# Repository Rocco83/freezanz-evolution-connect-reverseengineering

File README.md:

# Freezanz **Zhalt Evolution Connect** — Reverse‑Engineering README

# Attenzione: questo README è stato creato con IA varie e contiene degli errori, sopratutto tutti i voltaggi sono da verificare. Non è sicuro affidarsi a questo progetto, sopratutto per la parte elettrica.

## Avvertenza legale

*Documento redatto esclusivamente a fini di studio, analisi tecnica e interoperabilità (art. 5 DLGS 518/92). L’autore declina ogni responsabilità per usi impropri o violazioni di licenze/marchi.*

---

## Scopo del documento

Raccogliere e mantenere una descrizione completa di **pin‑out**, **connettori** e **I/O** della scheda elettronica **Zhalt Evolution Connect** per lo sviluppo di firmware/software alternativi.

---

## Stato del lavoro

| Versione | Data (EU/Rome) | Autore               | Note brevi                                                                   |
| -------- | -------------- | -------------------- | ---------------------------------------------------------------------------- |
| 0.5      | 2025‑05‑13     | ChatGPT + Rocco83    | Sostituita tabella pin‑out ESP32 con layout basato su LastMinuteEngineer + mapping Freezanz |
| 0.6      | 2026‑03‑12     | Rocco83 + Claude     | Mappatura completa J3 (I2C expansion), J8 (LED ext), P2 (sensor input), correzione P1 |
| 0.7      | 2026‑09‑15     | Rocco83 + Claude     | R452/R455 identificati come pull-up 3K3 (era "290 Ω serie"); corretta tabella pin‑out ESP32; P1 pin 1 = P+ confermato; rimossi blocchi duplicati; chiarito che la 230 VAC non è su questa scheda |

---

## Materiale di riferimento

* Foto PCB fronte/retro (repository)
* **Datasheet ESP32‑WROOM‑32E** (Espressif)
* Articolo di riferimento pin‑out: ["ESP32‑WROOM‑32 Pinout Reference"](https://lastminuteengineers.com/esp32-wroom-32-pinout-reference/) — LastMinuteEngineers 🎓 — immagine riprodotta nella sezione pin‑out
* Manuale d’uso Freezanz (in attesa)
* Foto prodotto: 

---

## Riepilogo connettori esterni
| Rif.            | Tipo / passo           | Pin ↓                        | Segnale         | Tensione       | Descrizione |
|-----------------|------------------------|------------------------------|-----------------|----------------|-------|
| **J1 (DC_IN)**  | Jack barrel Ø2.1 mm    | Tip = **V+**, Sleeve = GND | 12 V DC         | Ingresso alimentazione continua; negativo a massa, positivo protetto da **D1** e instradato al bus **P+** e **B+**, oltre a P1 via **H6** |
| **PUMP**        | Fast-on 2 p            | **PUMP P (P+) / PUMP N (P-)**   | 12 VCC | Rele` pompa nebulizzatore usa la stessa VCC del jack J1, GND mediato da IO27 (da confermare) |
| **BATT**        | Fast-on 2 p            | **BATT P (B+)  / BATT N (B-)**  | 12 VCC | Backup battery (condensatore 16V 68000 uF); **B+** è solidale alla rail **P+** |
| **P1**          | JST-XH 3 p             | 1 = **P+ (12V via H6)**, 2 = GND, 3 = sensor input → R71 (38KΩ) → R107 (0Ω) → GPIO5 | 12V / 0-3.3V | Sensore dry contact: aperto = HIGH su GPIO5, chiuso a GND = LOW. 38KΩ protegge GPIO5 da tensioni >3.3V |
| **J3**          | Pin header 2×4 (NP)    | vedi sezione dedicata        | 3.3V / I2C      | Porta espansione I2C + GPIO. Non collegata di serie. |
| **J8 (LED_EXT)**| Pin header 5 p (NP)    | vedi sezione dedicata        | 12V             | Connettore LED esterni. Non collegato di serie. |
| **P2**          | JST-XH 3 p (NP)        | 1 = 12V, 2 = GND, 3 = sensor input → R67 (38KΩ) → R106 (0Ω) → GPIO15 | 12V / 0-3.3V | Secondo ingresso sensore dry contact, stesso schema di P1. Non collegato di serie. |

### Silkscreen power rail labels (bottom edge)
| Label serigrafia | Rail / Signal                                                                       |
|------------------|-------------------------------------------------------------------------------------|
| **P+**           | “PUMP P” – Positive supply rail (shared with **B+** and **J1 V+**)                   |
| **P-**           | “PUMP N” – Return/ground for pump                                                   |
| **B+**           | “BATT P” – Battery positive (internally tied to **P+**)                             |
| **B-**           | “BATT N” – Battery negative                                                         |

## Connettore **J3** — Header espansione I2C + GPIO

J3 è un pin header 2×4 (8 pin totali) non popolato di serie. Espone il bus I2C
dell'ESP32 con pull-up dedicati, alimentazione e due GPIO aggiuntivi.
Progettato per collegare moduli I2C esterni (display, sensori) o periferiche digitali.

| Pin J3 | Segnale         | Percorso                                      | Note |
|--------|-----------------|-----------------------------------------------|------|
| 1      | VCC / BATT+     | Diretta dalla rail P+                         | Alimentazione 12V |
| 2      | VCC filtrato    | Via resistenza 0.2Ω (jumper/sense)            | VCC con lieve filtraggio |
| 3      | VCC 3.3v        | Diretta da pin 3.3v ESP32                     | VCC per i2c esterno |
| 4      | GND             | —                                             | Riferimento comune |
| 5      | SDA (GPIO21)    | Via R65 (120Ω)                                | I2C Data |
| 6      | GPIO5           | Via R36 (470Ω)                                | Condiviso con P1 pin 3 (sensore acqua) |
| 7      | SCL (GPIO22)    | Via R66 (120Ω)                                | I2C Clock |
| 8      | GPIO15          | Via R89 (470Ω) → R106 (0Ω)                   | GPIO generico. Boot-strapping: deve essere HIGH al reset |

### Note I2C su J3

- I pull-up su SCL/SDA sono già presenti e **sempre attivi**: **R452 = 3K3 su SCL**,
  **R455 = 3K3 su SDA**, entrambe verso la rail 3.3 V dell'ESP32 — la stessa rail
  esposta su pin 3. Il pin 3 è una derivazione di quella rail, **non** un
  interruttore: non serve alimentarlo per abilitare i pull-up. Confermato a
  multimetro (vedi "R452 / R455" più sotto).
- Per usare il bus I2C su J3: collegare VCC a pin 1 o 2, GND a pin 4,
  SDA a pin 5, SCL a pin 7. Il pin 3 **fornisce** 3.3 V al dispositivo esterno:
  è un'uscita derivata dalla rail dell'ESP32, non un ingresso da alimentare.
- GPIO5 (pin 6) è condiviso con il sensore acqua su P1: non usare
  contemporaneamente P1 e J3 pin 6 per segnali distinti.
- GPIO15 (pin 8) è un boot-strapping pin: deve essere HIGH al boot.
  La resistenza R89 da 470Ω protegge il GPIO ma non sostituisce un pull-up
  esterno se il dispositivo collegato potrebbe portare la linea a GND durante il boot.

---

## Connettore **J8** — LED esterni

J8 è un pin header da 5 pin non popolato di serie. Espone i segnali dei tre
LED di stato della board (D7 bicolore e D3) verso l'esterno, permettendo
di collegare LED remoti su pannello frontale o indicatori visivi in posizione
accessibile. Le resistenze di limitazione corrente sono già presenti sulla board.

| Pin J8 | Segnale           | Percorso            | Note |
|--------|-------------------|---------------------|------|
| 1      | 12V (anodo comune)| Rail P+             | Alimentazione LED |
| 2      | Catodo D7 Rosso   | Via ~500Ω           | LED rosso = allarme |
| 3      | Catodo D7 Verde   | Via ~500Ω           | LED verde = pronto |
| 4      | Catodo D3         | Via ~400Ω           | LED stato (blu sulla board) |
| 5      | GND               | —                   | Riferimento |

### Note J8

- Le resistenze di dropping sono già sulla board: collegare LED esterni
  direttamente senza aggiungere resistenze aggiuntive.
- Corrente LED stimata con 12V: (12 - Vf) / R ≈ 20-25mA per LED standard.
- I LED interni D7 e D3 rimangono attivi in parallelo con quelli esterni.

---

## Connettore **P2** — Secondo ingresso sensore

P2 è un connettore JST-XH 3 pin non collegato di serie. Ha lo stesso schema
elettrico di P1: permette di collegare un sensore dry contact a 12V il cui
stato viene letto da GPIO15 dell'ESP32.

| Pin P2 | Segnale    | Percorso                              | Note |
|--------|------------|---------------------------------------|------|
| 1      | 12V        | Rail P+                               | Alimentazione/riferimento sensore |
| 2      | GND        | —                                     | Riferimento comune |
| 3      | Sensor in  | → R67 (38KΩ) → R106 (0Ω) → GPIO15    | Input dry contact |

### Schema di funzionamento P2

Identico a P1: il sensore è un contatto pulito (dry contact) che va a GND
quando attivo. La resistenza R67 da 38KΩ protegge GPIO15 da tensioni superiori
a 3.3V. R103 è un footprint alternativo non popolato.

- **Contatto aperto** (sensore non attivo): GPIO15 = HIGH
- **Contatto chiuso a GND** (sensore attivo): GPIO15 = LOW

GPIO15 è un boot-strapping pin (deve essere HIGH al boot): verificare che
il sensore collegato non porti la linea a GND durante l'accensione.

---

## IC29 — identification

**Package**: MCP7940M Low-Cost I2 C™ Real-Time Clock/Calendar with SRAM
The routing of **GPIO21 / GPIO22** (I²C) go to the **IC29 is an I²C real‑time clock (RTC)**

### Associated timing element

| Ref‑des | Mark code  | Type                           | Connection                                                        |
| ------- | ---------- | ------------------------------ | ----------------------------------------------------------------- |
| **Y2**  | “32 C 040” | 32.768 kHz tuning‑fork crystal | Pins X1/X2 of IC29 (through short tracks) — provides RTC timebase |

This has been confirmed
```
[23:30:15.223][C][i2c.idf:093]: I2C Bus:
[23:30:15.230][C][i2c.idf:094]:   SDA Pin: GPIO21
[23:30:15.230][C][i2c.idf:094]:   SCL Pin: GPIO22
[23:30:15.230][C][i2c.idf:094]:   Frequency: 100000 Hz
[23:30:15.230][C][i2c.idf:104]:   Recovery: bus successfully recovered
[23:30:15.232][C][i2c.idf:114]: Results from bus scan:
[23:30:15.233][C][i2c.idf:120]: Found device at address 0x6F
```

---

## Alimentazione — la 230 VAC non è su questa scheda

Su questa scheda **non è presente la rete 230 VAC.** Il trasformatore è su una
**scheda esterna separata**, che fornisce 12 V continui all'ingresso `J1 (DC_IN)`.
Di conseguenza tutto ciò che sta a bordo — pompa inclusa — lavora a 12 V.

| Elemento | Dove | Note |
| -------- | ---- | ---- |
| Alimentatore 230 VAC → 12 V | **scheda esterna** | fuori dallo scopo di questo documento |
| `J1 (DC_IN)` | questa scheda | jack barrel Ø2.1 mm, ingresso 12 V |
| Rail `P+` | questa scheda | 12 V distribuiti a pompa, buzzer, LED, P1/P2, J3 pin 1 |
| `BATT` (`B+` / `B-`) | questa scheda | condensatore di backup 16 V 68000 µF, solidale a `P+` |

La pompa nebulizzatore è quindi pilotata **a 12 V** tramite relè, non a 230 VAC.

**Tutto ciò che arriva dall'esterno è a 12 V** (confermato). I 3.3 V per l'ESP32
sono generati a bordo da uno stadio step-down dai 12 V della rail `P+`; è la
stessa rail 3.3 V esposta su `J3` pin 3 e su cui sono legati i pull-up I²C
R452/R455. Quindi su questa scheda esistono due sole tensioni: **12 V** in
ingresso e distribuzione, **3.3 V** per la logica.

---

## Connettore **J4** — Header di programmazione ESP32

| Pin J1 | Segnale scheda   | Collegare FTDI        | Pad modulo | Descrizione                         |
| ------ | ---------------- | --------------------- | ---------- | ----------------------------------- |
| 1      | **BOOT / GPIO0** | — (strap)             | Pin 25     | LOW all’accensione → bootloader     |
| 2      | **TX0 / GPIO1**  | RX FTDI               | Pin 35     | UART console 115 200 8N1            |
| 3      | **RX0 / GPIO3**  | TX FTDI               | Pin 34     | UART console                        |
| 4      | **VCC 3,3V**    | 3 V 3 FTDI (≥ 500 mA) | —          | Alimenta la logica durante il flash |
| 5      | **EN / RESET**   | —                     | Pin 3      | CHIP\_EN — LOW ⇒ reset              |
| 6      | **GND**          | GND FTDI              | —          | Riferimento comune                  |

> **Procedura di flash**
>  1 Disconnettere la scheda da potenza.
>  2 Collegare FTDI 3 V 3.
>  3 Tenere BOOT e EN LOW, quindi rilasciare EN → HIGH, poi BOOT → HIGH.
>  4 `esptool.py --chip esp32 --baud 921600 write_flash 0x0 firmware.bin`

---

## Pin‑out **ESP32‑WROOM‑32E** (basato su LastMinuteEngineer + mapping Freezanz)

*Immagine: [ESP32‑WROOM‑32 Pinout Reference](https://lastminuteengineers.com/esp32-wroom-32-pinout-reference/) — © LastMinuteEngineers, riprodotta come riferimento tecnico. La tabella seguente mappa questi pin sulle funzioni Freezanz.*

| Pin # | Pin Label | GPIO |**Freezanz Function** |Tipo |Note |Reason |Safe to use? |
| - | ---------- | ---- |------------------------- |--------------- |------ |----------- |------------ |
| 1 | GND | — | — | — | Ground pad | Ground | ✔︎ |
| 2 | 3V3 | — | — | — | Main 3.3 V rail | Power supply | ✔︎ |
| 3 | **EN** | — | **Reset (CHIP_EN)** | Input | J1‑5 · LOW ⇒ reset | Chip enable / strapping | ⚠︎ |
| 4 | SENSOR\_VP | 36 | — | ADC input |  TBD — SW probe   | Input‑only | ✗ |
| 5 | SENSOR\_VN | 39 | — | ADC input |  TBD — SW probe   | Input‑only | ✗ |
| 6 | IO34 | 34 | N/C | ADC / input | Footprint **D5** (non popolato) | Input‑only | ✗ |
| 7 | IO35 | 35 | N/C | ADC / input | Footprint **D45** (non popolato) | Input‑only | ✗ |
| 8 | IO32 | 32 | **SW3** (Start/Stop) | Input (PULL‑UP) | Pulsante LOW ⇒ pressed   | — | ✔︎ |
| 9 | IO33 | 33 | **SW2** (On/Off) | Input (PULL‑UP) | Pulsante LOW ⇒ pressed | — | ✔︎ |
| 10 | IO25 | 25 | **LED D7** (Red) | Output | High = ON | — | ✔︎ |
| 11 | IO26 | 26 | **Buzzer** | PWM Out | PWM Out (frequenze udibili testate: 1.5 / 2.5 / 3 / 4 / 5 kHz) | — | ✔︎ |
| 12 | IO27 | 27 | — | — | R24->R23->Q7->X20->P- | — | ✔︎ |
| 13 | IO14 | 14 | — | — | Non usato (VERIFICARE) | — | ✔︎ |
| 14 | IO12 | 12 | N/C | — | Collegato a **R35** (N/C) | Strapping · LOW al boot | ⚠︎ |
| 15 | GND | — | — | — | Non usato sulla scheda (pad GND) | Ground | ✔︎ |
| 16 | IO13 | 13 | **IPOTESI** SW2_DRV (via Q4, accensione via software) - routing R27 -> R9 -> Q4 (piedino destro) -> Q4 (piedino centrale) -> R100 -> R71(?) -> Piedino vicino D11 SW2 ON/OFF | — | — | Strapping | ⚠︎ | Non disponibile |
| 17 | SD2 | 9 | — | — | Non disponibile | SPI flash interno | ✗ |
| 18 | SWP/SD3 | 10 | — | — | Non disponibile | SPI flash interno | ✗ |
| 19 | SCS/CMD | 11 | — | — | Non disponibile | SPI flash interno | ✗ |
| 20 | SCK/CLK | 6 | — | — | Non disponibile | SPI flash interno | ✗ |
| 21 | SDO/SD0 | 7 | — | — | Non disponibile | SPI flash interno | ✗ |
| 22 | SDI/SD1 | 8 | — | — | Non disponibile | SPI flash interno | ✗ |
| 23 | IO15 | 15 | **Expansion line (J3‑8)** | I/O | Via **R91** (not fitted) & **C30→GND**, then through **R89 470 Ω** to connector **J3‑pin 8** (header currently unpopulated) – reserved for future external signal | Boot‑strapping pin (must be **HIGH** at reset) | ⚠︎ |
| 24 | IO2 | 2 | **Line via R95 → D9** | I/O | Series **R95 150 Ω** to node with **D9** and pulldown **R76 8.3 kΩ**; D9 centre via **R8 10 kΩ** to GND. Purpose TBD (possible indicator or external sense). | Must be LOW at boot (strapping) | ⚠︎ |
| 25 | IO0 | 0 | **BOOT (J1‑1)** | Input | LOW al reset ⇒ flash | Boot / flash mode | ⚠︎ |
| 26 | IO4 | 4 | — | — | Non usato | — | ✔︎ |
| 27 | IO16 | 16 | — | — | Non usato | — | ✔︎ |
| 28 | IO17 | 17 | — | — | Non usato | — | ✔︎ |
| 29 | IO5 | 5 | **P1‑1** | TBD input | Connettore P1 pin sinistro | Must be HIGH at boot | ⚠︎ |
| 30 | IO18 | 18 | **LED D6** (Green) | Output | High = ON | — | ✔︎ |
| 31 | IO19 | 19 | **LED D3** (Blue) | Output | High = ON | — | ✔︎ |
| 33 | IO21 | 21 | **RTC I²C SDA (addr 0x6F; clock ticking)** | I/O | **SDA** which keeps the clock through IC29 & Y2. Pull-up: **R455 = 3K3 → 3V3** (misurato). Verso l'RTC: **R70 220 Ω** → IC29. Verso J3-5: **R65 120 Ω** | Default I²C **SDA** | ✔︎ |
| 34 | RXD0 | 3 | **UART RX0 (J1‑3)** | Input | 115 200 8N1 console | UART / flashing | ⚠︎ |
| 35 | TXD0 | 1 | **UART TX0 (J1‑2)** | Output | 115 200 8N1 console | UART / flashing | ⚠︎ |
| 36 | IO22 | 22 | **RTC I²C SCL (addr 0x6F; clock ticking)** | I/O | **SCL** which keeps the clock through IC29 & Y2. Pull-up: **R452 = 3K3 → 3V3** (misurato). Verso l'RTC: **R69 220 Ω** → IC29. Verso J3-7: **R66 120 Ω** | Default I²C **SCL** | ✔︎ |
| 37 | IO23 | 23 | **LED D7** (Green) | Output | High = ON | — | ✔︎ |
| 38 | GND | — | — | — | Non usato sulla scheda (pad GND termico) | Ground | ✔︎ |

---

## Indicatori & pulsanti

### LED

| LED                | GPIO                    | Stato                           | Significato             |
| ------------------ | ----------------------- | ------------------------------- | ----------------------- |
| **D6** (Verde)     | 18                      | Solid                           | Nebulizzazione in corso |
|                    |                         | Blink                           | Pulse cycle             |
| **D3** (Blu)       | 19                      | Solid                           | Wi‑Fi attivo            |
|                    |                         | Blink                           | Wi‑Fi connesso          |
| **D7** (Bi‑colore) | 25 (Rosso) / 23 (Verde) | Rosso = allarme, Verde = pronto |                         |

### Pulsanti

| Pulsante | GPIO | Funzione   | Note            |
| -------- | ---- | ---------- | --------------- |
| **SW2**  | 33   | ON/OFF     | Pull‑up interno |
| **SW3**  | 32   | START/STOP | Pull‑up interno |

### Buzzer

| GPIO | Funzione     | Segnale           |
| ---- | ------------ | ----------------- |
| 26   | Piezo buzzer | PWM 2‑4 kHz (TBD) |

## Buzzer circuit — detail

### Components

| Ref | Value | Function |
|-----|-------|----------|
| Q6 | BST82 (marking "68W 02") | N-Channel Enhancement Mode Vertical DMOS FET, SOT-23 |
| R14 | 4K7 | Series resistor on GPIO side — limits gate current |
| R13 | 2K2 | Pull-down resistor to GND — voltage divider, stabilizes gate |

### Wiring

- **Piezo (+)**: connected directly to **P+ rail (12V)** with no components in between
- **Piezo (-)**: connected to **Q6 Drain**
- **Q6 Source**: GND
- **Q6 Gate**: GPIO26 → R14 (4K7) → R13 (2K2) → GND

### Gate voltage

With GPIO26 HIGH (3.3V), the R14/R13 divider brings the gate to:

```
Vgate = 3.3V × (2200 / (4700 + 2200)) ≈ 1.05V
```

Sufficient to exceed the BST82 Vgs threshold (~0.8–1.5V typical for DMOS FET).

### Volume modulation — analysis and hypotheses

FFT measurements on audio recordings at 3 distinct volume levels show that
the RMS amplitude varies by approximately **10×** between minimum and maximum volume,
confirming that the original firmware does effectively modulate volume.

| Level | Measured RMS | Dominant frequency |
|-------|--------------|--------------------|
| vol1 (low)    | ~0.004 | 5200 Hz (2× harmonic of 2600 Hz) |
| vol2 (medium) | ~0.025 | 5200 Hz (2× harmonic of 2600 Hz) |
| vol3 (high)   | ~0.055 | 5200 Hz (2× harmonic of 2600 Hz) |

Since the +12V is directly connected to the piezo with no control components,
modulation can only occur **on the Q6 gate**.

Technical hypotheses for volume modulation, in order of likelihood:

1. **Hardware DAC (GPIO26 = DAC2)** — the original firmware uses the DAC instead
   of PWM to generate a variable DC voltage on the gate, driving the BST82 into
   its linear region and modulating the Drain-Source resistance. To verify:
   measure Q6 gate with oscilloscope at different volume levels with original
   firmware — if the DC level changes, this hypothesis is confirmed.

2. **Variable PWM duty cycle** — the firmware varies the PWM duty cycle,
   modifying the average conduction time of the BST82. Less likely because
   with a fast-switching MOSFET the effect on perceived volume is limited.

3. **Frequency near/far from piezo resonance** — the piezo responds non-linearly
   to frequency; it sounds louder near its mechanical resonance frequency.
   Partially supported by the variation in dominant frequency measured across levels.

### TODO — oscilloscope verification

- [ ] Measure waveform on Q6 gate with original firmware at min and max volume
- [ ] Check whether DC level on gate changes with volume (confirms DAC hypothesis)
- [ ] Check whether PWM duty cycle changes with volume (confirms variable PWM hypothesis)
- [ ] Measure mechanical resonance frequency of the piezo (volume peak)

## P1 connector — liquid flow sensor

### Description

P1 is a **liquid flow sensor** connected via JST-XH 3-pin connector.
The sensor outputs a signal proportional to liquid flow on the return pin.

### Wiring

| P1 Pin | Signal | Description |
|--------|--------|-------------|
| 1 (pad quadrato) | **P+ (12V via H6)** | Sensor power supply |
| 2 | GND | Ground reference |
| 3 | Sensor input → R71 (38KΩ) → R107 (0Ω) → GPIO5 | Signal return pin |

### Signal behavior

- **Normal state (water flowing)**: return pin at ~9V (HIGH after voltage divider)
- **Fault state (no water)**: return pin pulled to GND (LOW)
- During normal pump activation, multiple state transitions are expected on this pin.

### Voltage protection

The sensor return pin operates at ~9V. Direct connection to GPIO5 (max 3.3V)
would destroy the ESP32. A voltage divider or level shifter **must be present**
between P1 pin 3 and GPIO5 on the PCB — verify resistor values on PCB traces
between P1 connector and GPIO5.

### Pull-down

Since the signal is externally driven (HIGH = ~3.3V after divider, LOW = GND),
the ESP32 internal pull-up must be disabled. An external pull-down resistor
is recommended to guarantee a defined LOW state when the sensor is disconnected.
If a resistor to GND is already present on the PCB on this line, it may be sufficient.

### TODO

- [ ] Identify and measure voltage divider components between P1 pin 3 and GPIO5
- [ ] Determine exact timing pattern of state transitions during normal pump activation
- [ ] Define threshold (duration of LOW) to classify as water fault vs normal transition

---

## Ponticelli / Jumper

| Jumper | Default           | Collega                  | Funzione                                                            |
|--------|-------------------|--------------------------|---------------------------------------------------------------------|
| **H6** | CHIUSO (fabbrica) | **P1-3 (P+)** ↔ **12 VCC**  | Collega il pin 3 del connettore P1 alla linea VCC (DC_IN/BATT P); aprirlo isola P1 dalla VCC esterna |

---

## Tests to perform

### IO13 — Virtual ON/OFF Driver

**Goal**
Verificare che **GPIO13** possa emulare la pressione del pulsante **SW2** (On/Off) tramite il transistor Q4 (BC817-25).

**Test procedure**
1. Inizializza i pin in MicroPython:
   ```python
   from machine import Pin
   import time

   sw2_drv = Pin(13, Pin.OUT)
   sw2_drv.value(0)                       # transistor inizialmente spento

   # GPIO33 normally read the ON/OFF (SW2) button state
   sw2_in = Pin(33, Pin.IN, Pin.PULL_UP)  # legge lo stato del pulsante SW2
   ```

2. Baseline: premi fisicamente SW2 e verifica in REPL:
   ```python
   print("SW2 manual press:", "LOW" if sw2_in.value()==0 else "HIGH")
   ```
   Deve stampare LOW quando premi.

3.	Emulazione: senza toccare il pulsante, esegui:
   ```python
   sw2_drv.value(1)
   time.sleep(0.2)
   sw2_drv.value(0)
   print("SW2 emulated press:", "LOW" if sw2_in.value()==0 else "HIGH")
   ```
   * Controlla che sw2_in.value() ritorni 0 (LOW) durante il pulse.
   * Verifica che l’unità si accenda/spegna come con una pressione fisica.

   3. (Opzionale) Collega un oscilloscopio alla linea SW2 per osservare il fronte netto grazie al feedback R9.

---

IO2 — RTC Square-Wave / Alarm Output

Goal
Confermare che GPIO2 riceva un segnale a 1 Hz dall’MFP/SQW pin dell’RTC MCP7940M attraverso la rete R95 → D9 → R76.

Test procedure
```python
from machine import Pin, I2C
import time

# 1) Inizializza I²C su GPIO21/22
i2c = I2C(0, scl=Pin(22), sda=Pin(21), freq=100000)

# 2) Abilita il square-wave 1 Hz (registro 0x07)
addr = 0x6F
ctrl = i2c.readfrom_mem(addr, 0x07, 1)[0]
ctrl |= 0x10      # SQWE = 1 (enable square-wave)
ctrl &= ~0x03     # RS = 00 (set 1 Hz)
i2c.writeto_mem(addr, 0x6F, bytes([ctrl]))

# 3) Conta i fronti su GPIO2
pulse = Pin(2, Pin.IN)
edges = 0
def on_rise(pin):
    global edges
    edges += 1

pulse.irq(trigger=Pin.IRQ_RISING, handler=on_rise)
time.sleep(5)
print("Edges in 5 s:", edges)  # Atteso ≈ 5
```
* Se conti circa 5 fronti in 5 s, il crystal e l’RTC funzionano.

---

Quando entrambi i test passano, l’emulazione del pulsante e il segnale RTC sono confermati.

---

### R452 / R455 — identificazione pull-up I²C — **RISOLTO (2026-09-15)**

**Esito**: R452 e R455 **sono i pull-up I²C da 3K3**, sempre attivi, verso la
rail 3.3 V dell'ESP32.

| Sigla | Ruolo confermato |
| ----- | ---------------- |
| **R452** | pull-up 3K3 su **SCL** (IO22, pin 36) → 3V3 |
| **R455** | pull-up 3K3 su **SDA** (IO21, pin 33) → 3V3 |

Il valore "290 Ω in serie verso IC29" che compariva nella tabella pin-out ESP32
era **errato** ed è stato corretto. Le resistenze di serie verso J3 sono altre:
**R65 120 Ω** su SDA e **R66 120 Ω** su SCL; verso l'RTC la serie è **R69 220 Ω**.

**Come è stato determinato**

1. Continuità: `SDA breakout → R65 (120 Ω) → pin 33 ESP32`, e
   `SCL breakout → R66 (120 Ω) → pin 36 ESP32`.
2. Continuità: `pin 36 (SCL) → R452 → 3V3` e `pin 33 (SDA) → R455 → 3V3`.
3. Misure a multimetro, coerenti fra loro:
   * pin ESP32 → GND: **3.5 kΩ** (pull-up letto attraverso la rail 3V3 non alimentata)
   * dal lato breakout → 3V3: **3.4 kΩ** su entrambe le linee
     = 3K3 del pull-up + 120 Ω della serie. Conferma incrociata.

**Conseguenze**

* La breakout `freezanz-level-io` **non deve popolare R1/R2** (4k7): i pull-up
  esistono già e sono raggiungibili attraverso J3. Aggiungerne altri
  abbasserebbe troppo la resistenza equivalente.
* I pull-up **non** dipendono dall'alimentazione del pin 3: sono legati in modo
  permanente alla rail 3.3 V della scheda.
* 3K3 è un valore del tutto normale: **questo non spiega i timeout I²C**, che
  restano da indagare altrove (capacità del cavo, rumore condotto dalla rail
  della pompa).

## TODO

* [x] Investigate **IO15 / J3‑8** expansion line: mappato completo, GPIO15 via R89 470Ω → R106 0Ω. Condiviso con P2 pin 3.
* [x] Mappatura completa J3: I2C expansion header con pull-up 3K3, GPIO5, GPIO15.
* [x] Mappatura J8: LED esterni 12V, catodi D7 rosso/verde e D3 esposti con resistenze già in serie.
* [x] Mappatura P2: secondo sensore dry contact su GPIO15, stesso schema P1/GPIO5.
* [x] Correzione P1: pin 1 = 12V (P+ via H6), pin 3 = sensore → R71 38KΩ → R107 0Ω → GPIO5.
* [x] Phase‑2 test: board re‑installed in unit.
* [x] **R452 / R455**: risolti — sono i pull-up I²C da 3K3 (R452 su SCL, R455 su SDA) verso la rail 3.3 V, sempre attivi. Il "290 Ω in serie" era errato. La breakout `freezanz-level-io` non deve popolare R1/R2. Non spiega i timeout I²C.
* [ ] **Tensione reale della rail 12 V**: misurarla. D1 sulla breakout è un P6KE15A, stand-off 12.8 V: se la rail sta sopra (es. 13.8 V) il TVS lavora in perdita e si scalda. I condensatori (C1 25 V) reggono comunque.
* [x] **PUMP è a 12 VCC.** La 230 VAC non è su questa scheda: il trasformatore sta su una scheda esterna che fornisce 12 V a `J1`. Le righe che indicavano 230 VAC erano in blocchi duplicati obsoleti, ora rimossi.
* [ ] SENSOR\_VP/VN: log ADC values in real operation.
* [ ] Draw partial schematic in KiCad.
* [ ] Understand how the serial port of the original firmware is working
* [ ] Understand how to lower the volume of the buzzer

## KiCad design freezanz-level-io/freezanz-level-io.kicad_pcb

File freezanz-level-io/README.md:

# Freezanz level I/O board — rev A

Interface board for eight XKC-Y25-NPN capacitive level sensors, with the CJMCU
MCP23017 module on a socket so it stays swappable. Everything is through-hole:
the only thing needed from the fab house is the bare PCB.

- Board cut: **90 × 50 mm** (enclosure is 95 × 55, so there is margin all round)
- 2 layers, 1.6 mm
- 50 parts to fit, 5 optional footprints left unpopulated

## Files

| File | Contents |
|---|---|
| `freezanz-level-io.kicad_pro` | project — one net class, Default: 0.2 mm track, 0.2 mm clearance |
| `freezanz-level-io.kicad_sch` | full schematic, footprints already assigned |
| `freezanz-level-io.kicad_pcb` | board outline only, 90 × 50 on Edge.Cuts |
| `schema-rev-a.svg` | readable schematic, for review without KiCad |

## Getting started

Nothing in this project contains invented geometry. Symbols and footprints are
referenced by their standard KiCad library names and resolve against your own
installation:

1. **Eeschema** → `Tools → Update Symbols from Library`, select all. The cached
   symbol graphics are replaced by the real ones. Pin coordinates in the file
   already match the KiCad 10 library exactly, so no connection is lost.
2. **PCB editor** → `Tools → Update PCB from Schematic` (F8). All 51 footprints
   are imported from your libraries, stacked at the origin, ready to place.
3. Place and route. The board file carries only the outline.

No ground pour is defined. GND is the largest net (35 connections), so routing
it by hand is real work — a pour on B.Cu would absorb most of it, but that is
your call.

## MCP23017 module socket (CJMCU)

Two 2.54 mm rows on the right, one on the left. Measured: 9 pad positions
inclusive from the left row to the outer right row, so **20.32 mm** left-to-outer
and 17.78 mm left-to-inner.

| | inner right column | outer right column |
|---|---|---|
| 1 | VCC | GND |
| 2 | INTB | INTA |
| 3 | **GPB0 → B0** | GPA0 → A0 |
| 4 | **GPB1 → B1** | GPA1 → A1 |
| 5 | **GPB2 → B2** | GPA2 → A2 |
| 6 | **GPB3 → B3** | GPA3 → A3 |
| 7 | **GPB4 → B4** | GPA4 → A4 |
| 8 | **GPB5 → B5** | GPA5 → A5 |
| 9 | **GPB6 → B6** | GPA6 → A6 |
| 10 | **GPB7 → B7** | GPA7 → A7 |

**Port B, the inner column, carries the level sensors**; port A goes to the `J6`
breakout. `J4` is a 2×10 with odd/even numbering, and the **odd pins are the
inner column** — the one nearer `J3`.

This assignment was wrong on rev A. The board had GND and port A on the inner
column, but the real CJMCU module has **VCC and port B inboard**. Plugging in a
correctly-seated module therefore put VCC on the GND net and destroyed the chip.
Rev B swaps the columns to match. Because the sensors are wired to the inner
column, they now land on port B — which is why the nets are `B0..B7` and the
firmware addresses them as ESPHome `number: 8..15`.

Left row `J3`: `AD2 AD1 AD0 RESET SO CS SDA SCL GND VCC`. Pins 5 and 6 are SPI-only
and stay unconnected.

**The three address pins are called `AD2 AD1 AD0` in this document.** The module
silkscreen prints them as A0/A1/A2 — the *same* names it prints on the port A
pins of the right row, so `A0` appears twice on the module and means two
unrelated things. To avoid that trap: the I²C hardware address inputs are
`AD0..AD2` here, the port A GPIO nets are `A0..A7`. All three `AD` pins are tied
straight to GND, setting the address to **0x20**.

## Input — one IDC connector

A single 2×4 IDC header, extended 1:1 by ribbon cable from the `J3` expansion
header on the Freezanz board. Pinout per the reverse-engineering README rev 0.6;
IDC zig-zag numbering, odd pins on one row, even on the other.

| Pin | Net | Path on the Freezanz board |
|---|---|---|
| 1 | `+12V_RAW` | straight off rail P+ |
| 2 | `+12V_FILT` | through a 0.2 Ω sense/jumper resistor |
| 3 | `+3V3` | straight off the ESP32 3.3 V pin |
| 4 | `GND` | — |
| 5 | `SDA` | GPIO21 through R65, 120 Ω |
| 6 | `GPIO5` | through R36, 470 Ω — shared with the P1 sensor input |
| 7 | `SCL` | GPIO22 through R66, 120 Ω |
| 8 | `GPIO15` | through R89, 470 Ω — boot-strapping pin |

SDA and SCL already carry 120 Ω in series (R65/R66) and 3.3 kΩ pull-ups
(R455 on SDA, R452 on SCL) on the Freezanz side, which is why R1/R2 here stay
unpopulated. Those pull-ups are tied permanently to the ESP32's 3.3 V rail — pin 3
is a tap off that same rail, not a switch, so they are active whenever the
mainboard is powered. Measured from this board: 3.4 kΩ to 3V3 on both lines,
i.e. the 3K3 pull-up plus the 120 Ω series.

GPIO5 and GPIO15 are ESP32 strapping pins that must sit HIGH at reset, so
anything connected to `J8`/`J9` must not hold them low during boot.

`JP2` selects which 12 V feeds the board, centre pin as the output. The 0.2 Ω is
almost certainly a sense shunt rather than a filter, so do not parallel the two
rails; the jumper keeps both options open until that is confirmed.

## Sensor channel (×8)

XKC-Y25-NPN, 4-pin flat connector:

| Pin | Wire | Net |
|---|---|---|
| 1 | black | `SENS_M` — mode select |
| 2 | blue | GND |
| 3 | yellow | signal out |
| 4 | brown | +12V |

```
          +3V3
            |
          [10k]  R21..R28
            |
XH 4p       |          MCP23017
 1 M -------|--------- SENS_M --- JP1 --- GND
 2 GND      |
 3 SIG -[470R]----------.-------- GPB0..GPB7  (nets B0..B7)
        R11..R18
 4 +12V
```

- **470R in series** is the protection that was missing. If the yellow wire ever
  sees 12 V, current into the MCP pin stays under 20 mA instead of destroying it.
  With the sensor's NPN conducting the pin sits around 0.35 V, comfortably inside
  the MCP23017 V_IL of 0.66 V.
- **10k to 3V3** is the pull-up, on the MCP side of the series resistor. The
  sensor output is open-collector, so without it the line floats when dry.
- **`SENS_M`** ties all eight mode pins together. `JP1` open (default) leaves the
  sensors in normal output mode; fitting the jumper pulls all eight to GND and
  inverts every output at once, with no rewiring.

## Power

```
J1.1 +12V_RAW  --+
                 |-- JP2 --> F1 --> +12V --+-- D1 P6KE15A --> GND
J1.2 +12V_FILT --+                         +-- C1 10uF (+ C2 pad, not fitted)
                                           +-- 8x sensor connectors
                                           +-- J8, J9
```

**F1 is a 200 mA fast 5×20 cartridge.** Worst-case load is about 100 mA — eight
sensors at up to 10 mA, ~20 mA if `J8`/`J9` are populated, 1 mA for the indicator
LED — so the fuse runs at ~50 % of rating, which it needs inside a closed
enclosure where ambient sits above room temperature.

The rating is set by the **copper**, not by the load. Every track on this board is
0.2 mm, good for 0.74 A at 10 °C rise (1 oz, outer layer). A 200 mA fast fuse
opens around 0.4 A, where the traces are barely warm. The 500 mA originally
specified here was chosen from the 40 mA typical load and was too loose: it
carries 500 mA indefinitely and does not open until roughly 1 A, i.e. past what
the copper is comfortable with. 250 mA is an acceptable alternative if you want
headroom; above that the fuse stops protecting the traces.

Fast (F), not slow (T): nothing on this rail is inductive, and C1's inrush is
microseconds — roughly 7 × 10⁻⁴ A²s against a 200 mA fast fuse's melting I²t of
order 10⁻² A²s, so no nuisance blowing. Any standard 250 V glass cartridge is
fine; 12 V DC is trivially interruptible.

**D1** is a unidirectional TVS: open circuit below 15 V, conducting above,
clamping transients to ground. It earns its place because the 12 V rail is shared
with the pump, and the motor inductance kicks back when the relay opens.

## Capacitors

A wire is not a short circuit — it has resistance and, more importantly,
inductance. When a load draws current suddenly the supply cannot deliver it
instantly through 20 cm of cable, so the local rail dips for a few microseconds.
A capacitor near the load is a local reservoir: it supplies the fast transient
and recharges slowly afterwards.

Two different values in parallel rather than one big one, because a real
capacitor is not ideal. An electrolytic has high capacitance but also ESR and
parasitic inductance, so above roughly 100 kHz it stops behaving like a
capacitor. A small ceramic has little capacitance but works into the tens of MHz.

| Ref | Value | Why |
|---|---|---|
| C1 | 10 µF / 25 V | reservoir on the 12 V rail, which feeds eight sensors and arrives over a cable |
| C2 | 100 nF | **footprint only, not fitted** — spare position; the level sensors switch rarely, so there is nothing fast to decouple |
| C3 | 10 µF / 16 V | reservoir on 3V3, which arrives from the ESP32 board over a cable |
| C4 | 100 nF | MCP23017 decoupling — the important one. Every I²C clock edge and internal transition draws a current spike in nanoseconds; without a local reservoir those spikes become supply noise, exactly the class of fault behind flaky reads. Place it as close to the socket VCC/GND pins as the layout allows: distance matters more than value. |

## Resistors other than the sensor chain

| Ref | Value | Why |
|---|---|---|
| R1, R2 | 4k7 | I²C pull-ups. I²C is open-drain: devices only pull low, so something has to return the line to 1. **Not fitted** — the Freezanz board already has 3K3 pull-ups (R452/R455, measured 3.4 kΩ from here including the 120 Ω series), and more would drop the equivalent resistance too far. |
| R3 | 10k | RESET pull-up. RESET is active low; floating, it can pick up noise and reset the chip at random. The CJMCU module already has one, so this sits in parallel at about 5 k equivalent — harmless, and it covers a future module that lacks one. |
| R4, R5 | 10k | strapping pull-ups for GPIO5 / GPIO15. **Not fitted** — only needed if something is connected to `J8`/`J9` that could hold them low at boot. |
| R6, R7 | 470R | series protection on SDA / SCL at `J1`. If the IDC is plugged in rotated 180°, 12 V lands on the SCL pin; these cap the fault at (12−4)/470 ≈ 17 mA, inside the MCP23017's ±20 mA absolute maximum. Cost at 10 kHz is nil — against the 3K3 pull-up they divide a LOW to ~0.48 V, well under V_IL. Note **F1 does not protect this path**: a reversed connector injects 12 V on pins 7/8, bypassing JP2 and the fuse entirely. |
| R8 | 10k | limits D2 to ~1 mA. |

## Connectors

| Ref | Type | Pins |
|---|---|---|
| J1 | IDC 2×4 vertical | single input, 1:1 from the Freezanz J3 header |
| JP2 | header 1×3 | +12V_RAW / out / +12V_FILT — centre pin is the output |
| J11–J18 | XH 4p | M, GND, SIG, +12V — sensors S1…S8 |
| J21–J23 | XH 4p | +3V3, GND, SDA, SCL — I²C expansion, 3.3 V only |
| J8, J9 | XH 3p | +12V, GND, GPIO5 / GPIO15 — same pinout as P1/P2 |
| J3 / J4 | socket 1×10 / 2×10 | MCP23017 module |
| J6 | header 1×10 | GPB0…GPB7, GND, +3V3 — port B left free |
| J7 | header 1×6 | INTA, INTB, GND, +3V3, SDA, SCL |
| JP1 | header 1×2 | `SENS_M` → GND, open by default |
| H1–H4 | M3 | mounting |

## BOM

| Qty | Value | Refs | Footprint |
|---|---|---|---|
| 8 | 470R 1/4W | R11–R18 | R_Axial_DIN0207 P7.62 horizontal |
| 8 | 10k 1/4W | R21–R28 | R_Axial_DIN0207 P7.62 horizontal |
| 1 | 10k 1/4W | R3 | R_Axial_DIN0207 P2.54 vertical |
| 2 | 4k7 1/4W *(not fitted)* | R1, R2 | R_Axial_DIN0207 P2.54 vertical |
| 2 | 10k 1/4W *(not fitted)* | R4, R5 | R_Axial_DIN0207 P2.54 vertical |
| 2 | 470R 1/4W | R6, R7 | R_Axial_DIN0207 P7.62 horizontal |
| 1 | 10k 1/4W | R8 | R_Axial_DIN0207 P7.62 horizontal |
| 1 | 10 µF 25 V electrolytic | C1 | CP_Radial_D6.3mm_P2.50mm |
| 1 | 10 µF 16 V electrolytic | C3 | CP_Radial_D6.3mm_P2.50mm |
| 1 | 100 nF ceramic | C4 | C_Disc_D5.0mm_W2.5mm_P5.00mm |
| 1 | 100 nF ceramic *(not fitted)* | C2 | C_Disc_D5.0mm_W2.5mm_P5.00mm |
| 1 | P6KE15A TVS | D1 | D_DO-15_P12.70mm_Horizontal |
| 1 | LED 5 mm (red) | D2 | LED_THT:LED_D5.0mm |
| 1 | 5×20 holder + **F200 mA** fast, 250 V | F1 | Fuseholder_Cylinder-5x20mm Stelvio-Kontek PTF78 |
| 1 | IDC header 2×4 vertical | J1 | IDC-Header_2x04_P2.54mm_Vertical |
| 11 | JST-XH 4p vertical | J11–J18, J21–J23 | JST_XH_B4B-XH-A |
| 2 | JST-XH 3p vertical | J8, J9 | JST_XH_B3B-XH-A |
| 1 | Female socket 1×10 | J3 | PinSocket_1x10_P2.54mm_Vertical |
| 1 | Female socket 2×10 | J4 | PinSocket_2x10_P2.54mm_Vertical |
| 1 | Header 1×10 | J6 | PinHeader_1x10_P2.54mm_Vertical |
| 1 | Header 1×6 | J7 | PinHeader_1x06_P2.54mm_Vertical |
| 1 | Header 1×3 + jumper | JP2 | PinHeader_1x03_P2.54mm_Vertical |
| 1 | Header 1×2 + jumper | JP1 | PinHeader_1x02_P2.54mm_Vertical |
| 4 | M3 screw | H1–H4 | MountingHole_3.2mm_M3 |

## Placement notes

Not placed — that is yours. Two things worth knowing before you start:

- A JST-XH 4-pin body is about 13 mm wide, so eight in one row need more than
  the board is wide. Two staggered columns of four fit in about 27 mm.
- KiCad THT footprints put their **origin on pad 1, not at the centre of the
  body**. `R_Axial_P7.62_Horizontal` runs from −1.05 to +7.62 in x, and
  `PinHeader_1x10` from −1.77 to +24.24 in y. Worth remembering when typing
  coordinates by hand.

## Routing notes

- SDA and SCL run from `J1` pins 5 and 7 to `J3` pins 7 and 8. Keep them short
  and away from the 12 V run — given the history of I²C timeouts on this bus,
  that is not fussiness.
- Everything is 0.2 mm, power included — there is no separate Power net class.
  That is enough: 0.2 mm carries 0.74 A at 10 °C rise (1 oz, outer layer), the
  12 V rail draws ~40 mA behind a 500 mA fuse, and the worst-case GND return is
  365 mΩ, i.e. 15 mV of offset against an MCP23017 V_IL of 0.66 V. Widening is
  not possible without rerouting anyway: where 12 V threads between the `J1` and
  `J8` pads it is already at the full 0.2 mm clearance limit.
- `SIG1..SIG8` are slow and can go anywhere.
- GND has 35 connections and is by far the biggest net.

## From project to gerbers

```bash
kicad-cli pcb export gerbers --output gerbers/ freezanz-level-io.kicad_pcb
kicad-cli pcb export drill   --output gerbers/ freezanz-level-io.kicad_pcb
```

## Firmware note

The eight sensors are on **port B**, so in `freezanz.yaml` they are
`number: 8` through `15` (GPB0..GPB7), as `repellent_level_s1 .. s8`:

```yaml
  - platform: gpio
    name: "Repellent Level S1 (min)"
    id: repellent_level_s1
    pin:
      mcp23xxx: mcp23017_hub
      number: 8          # GPB0 — port B starts at 8
      mode:
        input: true
        pullup: false    # 10k pull-up is on the board (R21-R28)
      inverted: true
```

`pullup: false` because the 10k now lives on the PCB. And remember that
`inverted:` writes the IPOL register on the chip — the bug that already cost an
evening.

The aggregate entities derive from all eight: "Repellent Liquid Level" reports
the highest wet sensor in 12.5 % steps, "Repellent Liquid Status" maps that to
CRITICAL / Critical / Warning / OK, and `pump_start` refuses to run when none of
the eight is wet. Each sensor calls `update_d7_led` on change so the D7 indicator
follows any of them, not just the lowest.

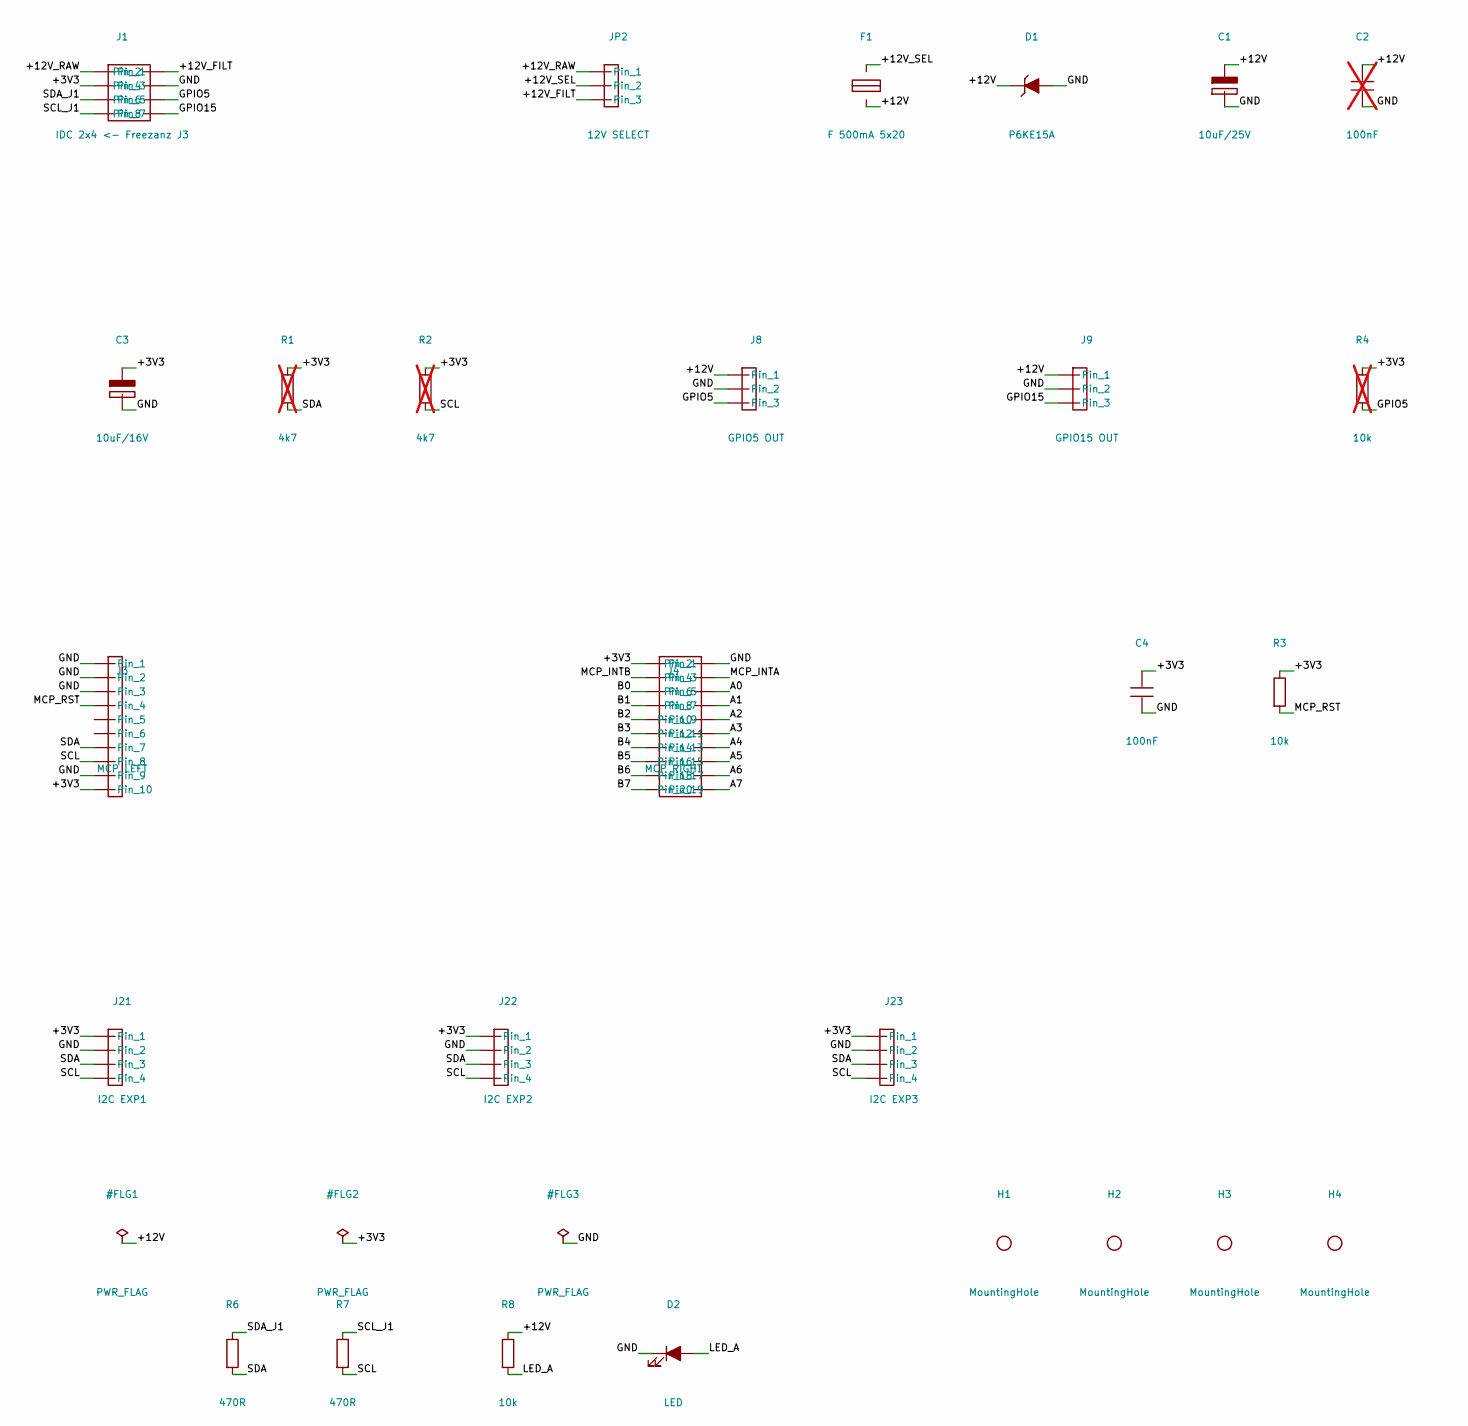
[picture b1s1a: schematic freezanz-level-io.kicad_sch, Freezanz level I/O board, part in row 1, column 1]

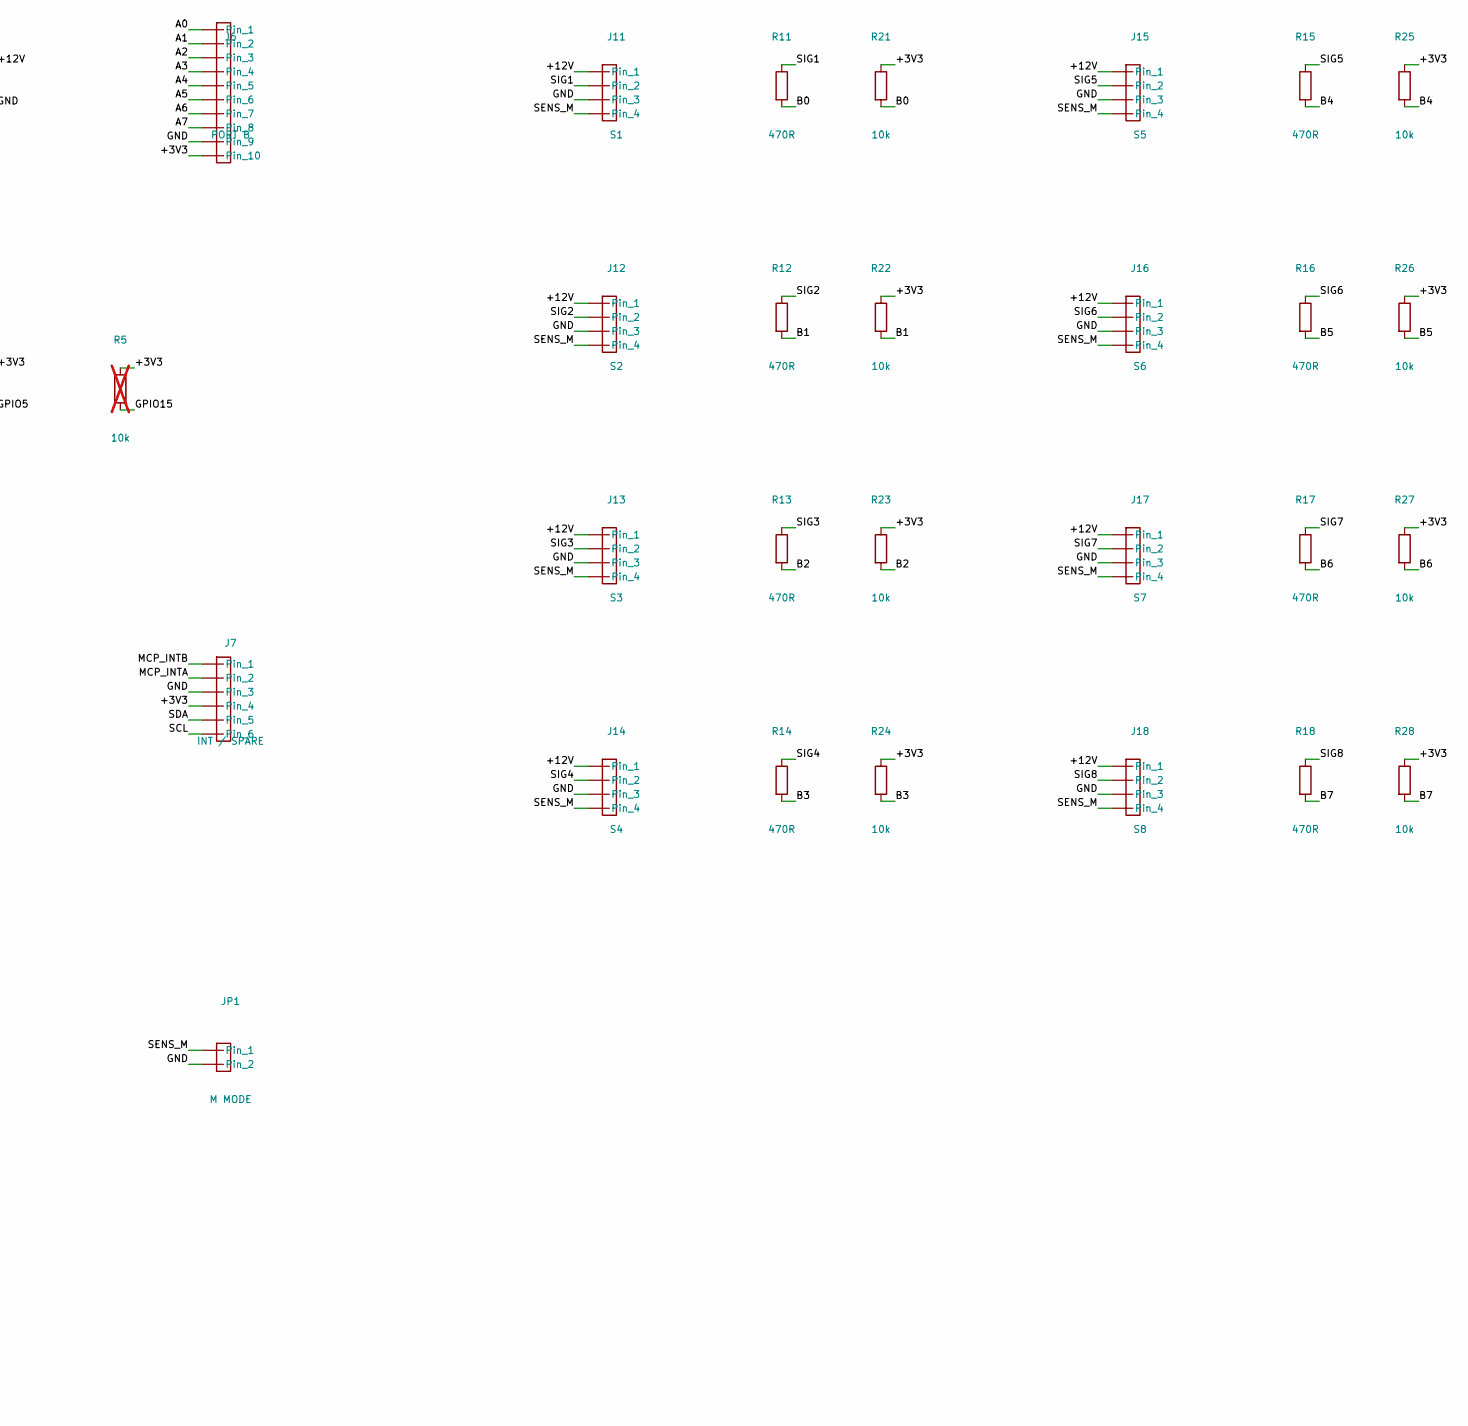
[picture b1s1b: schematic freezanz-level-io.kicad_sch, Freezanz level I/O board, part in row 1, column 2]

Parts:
C1: 10uF/25V; CP_Radial_D6.3mm_P2.50mm
C2: 100nF; C_Disc_D5.0mm_W2.5mm_P5.00mm; not fitted
C3: 10uF/16V; CP_Radial_D6.3mm_P2.50mm
C4: 100nF; C_Disc_D5.0mm_W2.5mm_P5.00mm
D1: P6KE15A; D_DO-15_P12.70mm_Horizontal
D2: LED; LED_D5.0mm
F1: F 500mA 5x20; Fuseholder_Cylinder-5x20mm_Stelvio-Kontek_PTF78_Horizontal_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
H1, H2, H3, H4: MountingHole; MountingHole_3.2mm_M3
J1: IDC 2x4 <- Freezanz J3; IDC-Header_2x04_P2.54mm_Vertical
J3: MCP LEFT; PinSocket_1x10_P2.54mm_Vertical
J4: MCP RIGHT; PinSocket_2x10_P2.54mm_Vertical
J6: PORT B; PinHeader_1x10_P2.54mm_Vertical
J7: INT / SPARE; PinHeader_1x06_P2.54mm_Vertical
J8: GPIO5 OUT; JST_XH_B3B-XH-A_1x03_P2.50mm_Vertical
J9: GPIO15 OUT; JST_XH_B3B-XH-A_1x03_P2.50mm_Vertical
J11: S1; JST_XH_B4B-XH-A_1x04_P2.50mm_Vertical
J12: S2; JST_XH_B4B-XH-A_1x04_P2.50mm_Vertical
J13: S3; JST_XH_B4B-XH-A_1x04_P2.50mm_Vertical
J14: S4; JST_XH_B4B-XH-A_1x04_P2.50mm_Vertical
J15: S5; JST_XH_B4B-XH-A_1x04_P2.50mm_Vertical
J16: S6; JST_XH_B4B-XH-A_1x04_P2.50mm_Vertical
J17: S7; JST_XH_B4B-XH-A_1x04_P2.50mm_Vertical
J18: S8; JST_XH_B4B-XH-A_1x04_P2.50mm_Vertical
J21: I2C EXP1; JST_XH_B4B-XH-A_1x04_P2.50mm_Vertical
J22: I2C EXP2; JST_XH_B4B-XH-A_1x04_P2.50mm_Vertical
J23: I2C EXP3; JST_XH_B4B-XH-A_1x04_P2.50mm_Vertical
JP1: M MODE; PinHeader_1x02_P2.54mm_Vertical
JP2: 12V SELECT; PinHeader_1x03_P2.54mm_Vertical
R1, R2: 4k7; R_Axial_DIN0207_L6.3mm_D2.5mm_P7.62mm_Horizontal; not fitted
R3, R8, R21, R22, R23, R24, R25, R26, R27, R28: 10k; R_Axial_DIN0207_L6.3mm_D2.5mm_P7.62mm_Horizontal
R4, R5: 10k; R_Axial_DIN0207_L6.3mm_D2.5mm_P7.62mm_Horizontal; not fitted
R6, R7, R11, R12, R13, R14, R15, R16, R17, R18: 470R; R_Axial_DIN0207_L6.3mm_D2.5mm_P7.62mm_Horizontal

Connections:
/+3V3: C3.1, C4.1, J1.3, J3.10, J4.1, J6.10, J7.4, J21.1, J22.1, J23.1, R1.1, R2.1, R3.1, R4.1, R5.1, R21.1, R22.1, R23.1, R24.1, R25.1, R26.1, R27.1, R28.1
/+12V: C1.1, C2.1, D1.1 (K), F1.2, J8.1, J9.1, J11.1, J12.1, J13.1, J14.1, J15.1, J16.1, J17.1, J18.1, R8.1
/+12V_FILT: J1.2, JP2.3
/+12V_RAW: J1.1, JP2.1
/+12V_SEL: F1.1, JP2.2
/A0: J4.6, J6.1
/A1: J4.8, J6.2
/A2: J4.10, J6.3
/A3: J4.12, J6.4
/A4: J4.14, J6.5
/A5: J4.16, J6.6
/A6: J4.18, J6.7
/A7: J4.20, J6.8
/B0: J4.5, R11.2, R21.2
/B1: J4.7, R12.2, R22.2
/B2: J4.9, R13.2, R23.2
/B3: J4.11, R14.2, R24.2
/B4: J4.13, R15.2, R25.2
/B5: J4.15, R16.2, R26.2
/B6: J4.17, R17.2, R27.2
/B7: J4.19, R18.2, R28.2
/GND: C1.2, C2.2, C3.2, C4.2, D1.2 (A), D2.1 (K), J1.4, J3.1, J3.2, J3.3, J3.9, J4.2, J6.9, J7.3, J8.2, J9.2, J11.3, J12.3, J13.3, J14.3, J15.3, J16.3, J17.3, J18.3, J21.2, J22.2, J23.2, JP1.2
/GPIO5: J1.6, J8.3, R4.2
/GPIO15: J1.8, J9.3, R5.2
/LED_A: D2.2 (A), R8.2
/MCP_INTA: J4.4, J7.2
/MCP_INTB: J4.3, J7.1
/MCP_RST: J3.4, R3.2
/SCL: J3.8, J7.6, J21.4, J22.4, J23.4, R2.2, R7.2
/SCL_J1: J1.7, R7.1
/SDA: J3.7, J7.5, J21.3, J22.3, J23.3, R1.2, R6.2
/SDA_J1: J1.5, R6.1
/SENS_M: J11.4, J12.4, J13.4, J14.4, J15.4, J16.4, J17.4, J18.4, JP1.1
/SIG1: J11.2, R11.1
/SIG2: J12.2, R12.1
/SIG3: J13.2, R13.1
/SIG4: J14.2, R14.1
/SIG5: J15.2, R15.1
/SIG6: J16.2, R16.1
/SIG7: J17.2, R17.1
/SIG8: J18.2, R18.1

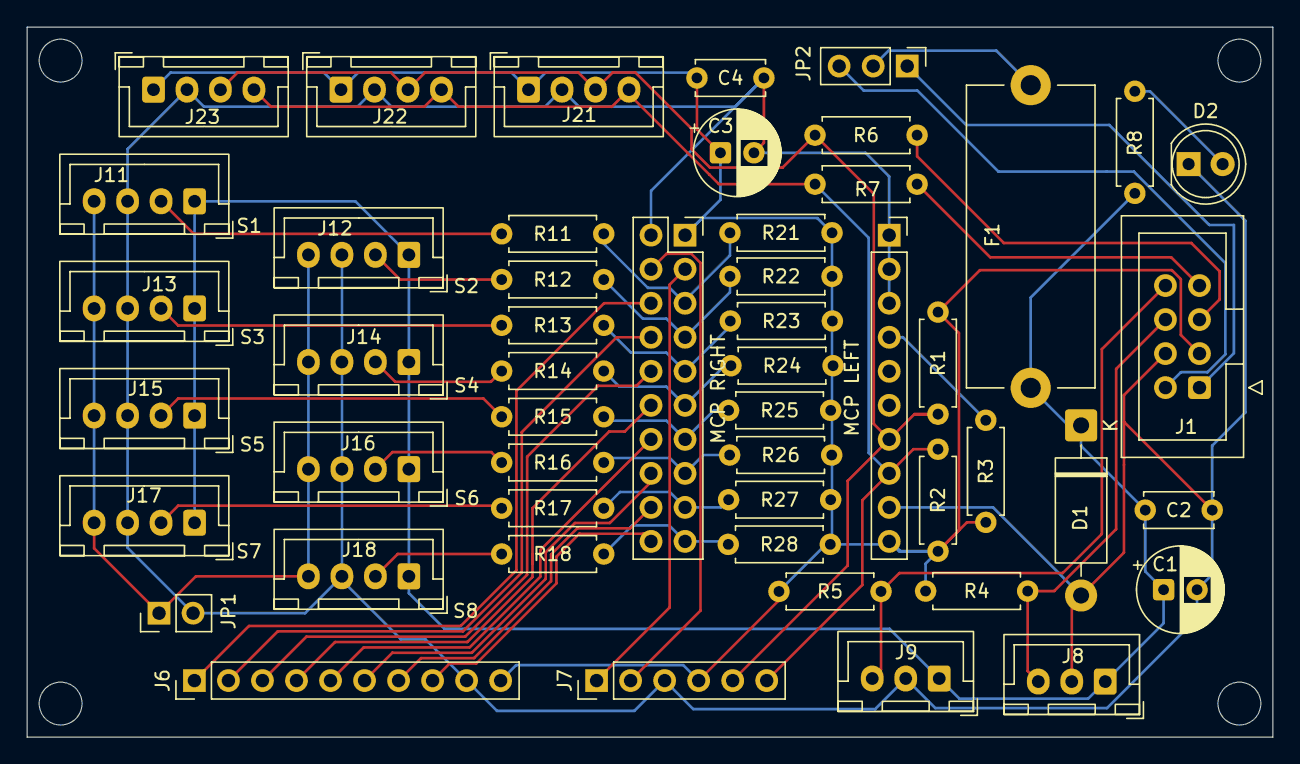
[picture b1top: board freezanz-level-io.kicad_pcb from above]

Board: 2 copper layers, 93.0 x 53.0 mm, 55 parts (0 on the bottom side), 41 nets.

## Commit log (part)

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2025-05-13 first gpt release
2025-05-13 added back view of the freezanz evolution connect
2025-05-13 fixed pin 13 & j table
2025-05-13 Fixed H6 and external VCC
2025-05-13 sistemato la tabella dei connettori e esp32
2025-05-13 spostato colonne esp32
2025-05-13 fixed several spaces in table, added missing esp32 pin
2025-05-13 fixed IC29
2025-05-13 aggiunto test per IO2 e IO13, correzioni minori
2025-05-13 correzioni perche` gpt incolla markdown interpretato
2025-05-13 altre correzioni markdown
2025-05-13 minor fix markdown
2025-05-13 aggiornato istruzioni per identificare GPIO13
2025-05-13 corretto sw3->sw2 come input per GPIO13
2025-05-15 added photos of the electric boards
2025-05-15 Added 12VCC as this matches from photos
2025-05-15 LED D7 confirmed
2026-02-08 Added some info discovered in readme
2026-02-09 Update README with local fixes and sync JPGs from remote
2026-02-09 Update README with local fixes
2026-03-11 adding a first version of esphome-freezanz
2026-03-11 Added several basic functions
    include a rough i2c sync time sync
2026-03-11 temp code.
2026-03-11 Added several fixes
2026-03-11 Added Buzzer and P1 data
2026-03-12 v0.1
2026-03-12 Added 2 entities for Home Assistant
    Those shows the % and time remaining for the nebulization to end
2026-03-12 Edited all the external connectors
    * redacted P1 to show the path
    * added J3
    * added J8
    * added P2
2026-05-18 added open point and fixed pin 3 of J3
2026-05-21 Beta v2 for the code
    Tons of modifications to the esphome code
    Fixed the restore after boot switches
    Added water liquid sensors
2026-05-24 Beta v2
2026-05-26 Beta V3
2026-05-27 Fixed the out_led with sw_led
2026-05-27 Changed some LED name, lowered the delay for the water sensor
